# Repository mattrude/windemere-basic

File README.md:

# Windemere Basic 6502 Computer

This is a proof of concept project to build a 65c02 computer from scratch.

This repository is broken up into 2 main sections, [Hardware](Hardware#readme) and [Software](SourceCode#readme).

## About

                 ┌───────────────────────────┐
                 │    WD65C02 Memory Map     │
                 ├───────┬───────────────────┤
                 │ $0000 │                   │
                 │       │   Zero Page RAM   │
                 │ $00ff │                   │
                 ├───────┼───────────────────┤
                 │ $0100 │///////////////////│
                 │       │////// Stack //////│
                 │ $01ff │///////////////////│
                 ├───────┼───────────────────┤
                 │ $0200 │                   │
                 │       │        RAM        │
                 │ $5fff │                   │
                 ├───────┼───────────────────┤
                 │ $6000 │                   │
                 │       │    W65C22S VIA    │
                 │ $600f │                   │
                 ├───────┼───────────────────┤
                 │ $6010 │                   │
                 │       │    (Not Used)     │
                 │ $7fff │                   │
                 ├───────┼───────────────────┤
                 │ $8000 │                   │
                 │       │        ROM        │
                 │ $ffff │                   │
                 └───────┴───────────────────┘

     ┌────────────────────────────────────────────────────────┐
     │                 Zero Page RAM Locations                │
     ├────────────────────────────────────────────────────────┤
     │ 0000: -- -- -- -- -- -- -- --  -- -- -- -- -- -- -- -- │
     │ 0010: -- -- -- -- -- -- -- --  -- -- -- -- -- -- -- -- │
     │ 0020: -- -- -- -- -- -- -- --  -- -- -- -- -- -- -- -- │
     │ 0030: -- -- -- -- -- -- -- --  -- -- -- -- -- -- -- -- │
     │ 0040: -- -- -- -- -- -- -- --  -- -- -- -- -- -- -- -- │
     │ 0050: -- -- -- -- -- -- -- --  -- -- -- -- -- -- -- -- │
     │ 0060: -- -- -- -- -- -- -- --  -- -- -- -- -- -- -- -- │
     │ 0070: -- -- -- -- -- -- -- --  -- -- -- -- -- -- -- -- │
     │ 0080: -- -- -- -- -- -- -- --  -- -- -- -- -- -- -- -- │
     │ 0090: -- -- -- -- -- -- -- --  -- -- -- -- -- -- -- -- │
     │ 00a0: -- -- -- -- -- -- -- --  -- -- -- -- -- -- -- -- │
     │ 00b0: -- -- -- -- -- -- -- --  -- -- -- -- -- -- -- -- │
     │ 00c0: -- -- -- -- -- -- -- --  -- -- -- -- -- -- -- -- │
     │ 00d0: -- -- -- -- -- -- -- --  -- -- -- -- -- -- -- -- │
     │ 00e0: -- -- -- -- -- -- -- --  -- -- -- -- -- -- -- -- │
     │ 00f0: 00 00 00 00 00 00 00 00  -- -- -- -- -- -- -- -- │
     └────────────────────────────────────────────────────────┘

## Required Tools/Software

### Software Used

* [KiCad](https://www.kicad.org/) - To create the Schematic and PCB
* [vasm](http://sun.hasenbraten.de/vasm/) - To compile the Source Code
* [miniPro](https://gitlab.com/DavidGriffith/minipro) - To upload the compiled binary to an eeprom
* [ClickCharts](https://www.nchsoftware.com/chart/index.html) - To create flowchart's for project documentation.

### Compiling from source

This source file expects the use of the vasm compiler found at: [sun.hasenbraten.de/vasm](http://sun.hasenbraten.de/vasm/)

To compile this code, run a command similer to:

    vasm6502_oldstyle -c02 -dotdir -Fbin main.asm -o main.bin

## System Images

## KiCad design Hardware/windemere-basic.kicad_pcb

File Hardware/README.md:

# Hardware

The file describes the layout of the board and how components are used.

## Control Logic

The control logic enables the different components connected to the registry according to the address requested by the 65C02 CPU. We accomplish this primarily by using 3 channels of a 4 channel NAND gate, the [74LS00](https://www.ti.com/lit/gpn/sn74ls00).

1. We start by flipping the bit of `A15` registry line by using two gates of a NAND gate. The inverted output is sent first to the `CS` (chip select) line of the EEPROM. This enables the ROM when the address requested on the registry bus is `$8000` or above and disables the chip when the address is below `$7FFF`.

2. The above inverted `A15` line from the NAND gate continues to one channel of a second NAND gate.  The other channel of this gate is connected to the `PHI2` clock signal, with it's output connected to the `CS` pin of the RAM chip.  The ROM chip also has it's `OE` (output enabled) pin connected to `A14`.  The `OE` pin is active low, so the RAM chip is only active between `$0000` to `$4FFF`.

3. The same inverted `A15` line from the first NAND gate is used a third time, this time in coordination with the `A14` line.  The output from this third gate connects to the `CS` pin of the WD65C22 VIA chip, enabling access in the `$6000`

## W65C22 VIA

The [W65C22](https://www.westerndesigncenter.com/wdc/documentation/w65c22.pdf) Versatile Interface Adapter (VIA) is a flexible I/O device used to connect to the [LCD Screen](#lcd-screen), [20-Button Keypad](#20-button-keypad) and used in software for it's timers.

As described in part 3 of the control logic section above, the VIA chip is accessed within the `$6000` address block.

```armasm
lda #$ff                ; Set all pins on port "B" to output
sta $6002               ; Store to port B on the W65C22
lda #$e1                ; top 3 pins/last, port "A" to output
sta $6003               ; Store to port A on the W65C22
```

## LCD Screen

The liquid crystal display (LCD) screen module is a Hitachi [HD44780](https://www.sparkfun.com/datasheets/LCD/HD44780.pdf) LCD controller is an alphanumeric dot matrix LCD controller developed by Hitachi in the 1980s. The character set of the controller includes ASCII characters, Japanese Kana characters, and some symbols in two 40 character lines.

```armasm
; To initialize the LCD screen via the W65C22

PORTB = $6000               ; W65C22 Register "B"
PORTA = $6001               ; W65C22 Register "A"
DDRB  = $6002               ; W65C22 Data Direction Register "B"
DDRA  = $6003               ; W65C22 Data Direction Register "A"
EN    = $80                 ; HD44780U LCD Starts data read/write
RW    = $40                 ; HD44780U LCD Enables Screen to read data
RS    = $20                 ; HD44780U LCD Registers Select

lcd_init:
    lda #$ff                ; Set all pins on port "B" to output
    sta DDRB
    lda #$e1                ; top 3 pins/last, port "A" to output
    sta DDRA
    lda #$38                ; 8-bit mode; 2-line display; 5x8 font
    jsr lcd_config
    lda #$c                 ; Display on; cursor on; blink off
    jsr lcd_config
    lda #$6                 ; Increment and shift cursor
    jsr lcd_config
    lda #$11                ; Clear the LCD display
    jsr lcd_config
    lda #$2                 ; Send cursor to line 1
    jsr lcd_config
loop:
    jmp loop                ; INIT is now complete

lcd_config:
    jsr lcd_wait             ; Jump to the lcd_wait subroutine
    sta PORTB
    lda #0                  ; Clear LCD RS/RW/EN bits
    sta PORTA
    lda #EN                 ; Set LCD EN (enable) bit
    sta PORTA
    lda #0                  ; Clear LCD RS/RW/EN bits
    sta PORTA
    rts                     ; Return from Subroutine

lcd_wait:
    pha                     ; Push Accumulator to Stack
    lda #%00000000          ; Set Port B as an input
    sta DDRB                ; Load the setting to Port "B"
lcd_busy:
    lda #RW                 ; Set port to Read/Write
    sta PORTA               ; Load the setting to Port "A"
    lda #(RW | EN)          ; Set port to Read/Write & Enable
    sta PORTA               ; Load the setting to Port "A"
    lda PORTB               ; Load Accumulator with Port "B"
    and #%10000000          ; Combine the above with $80
    bne lcd_busy            ; Jump back to the top of lcd_busy
    lda #RW                 ; Set port to Read/Write
    sta PORTA               ; Load the setting to Port "A"
    lda #%11111111          ; Port B is output
    sta DDRB                ; Load the setting to Port "B"
    pla                     ; Pull Accumulator from Stack
    rts                     ; Return from Subroutine
```

## 20-Button Keypad

For the 20-button keypad we use the [MM74C923](https://mm.digikey.com/Volume0/opasdata/d220001/medias/docus/1001/MM74C922,923.pdf) 20-Key Encoder connected to the above W65C22 VIA chip.

When a button is pressed, the chip will set the output as described below and set the `DA` (Data Available) pin, connected to the `CA1` pin on the W65C22, to high.

| W65C22 VIA  | MM74C923   |
| ----------- | ---------- |
| PA0 (pin 2) | A (pin 19) |
| PA1 (pin 3) | B (pin 18) |
| PA2 (pin 4) | C (pin 17) |
| PA3 (pin 5) | D (pin 16) |
| PA4 (pin 6) | E (pin 15) |

Below is a Simple key map with the left hand column showing the pin id as described above and the top row is the button id pressed.

|   | 0 | 1 | 2 | 3 | 4 | 5 | 6 | 7 | 8 | 9 | 10 | 11 | 12 | 13 | 14 | 15 | 16 | 17 | 18 | 19 |
|---|---|---|---|---|---|---|---|---|---|---|----|----|----|----|----|----|----|----|----|----|
| A | - | 1 | - | 1 | - | 1 | - | 1 | - | 1 | -  | 1  | -  | 1  | -  | 1  | -  | 1  | -  | 1  |
| B | - | - | 1 | 1 | - | - | 1 | 1 | - | - | 1  | 1  | -  | -  | 1  | 1  | -  | -  | 1  | 1  |
| C | - | - | - | - | 1 | 1 | 1 | 1 | - | - | -  | -  | 1  | 1  | 1  | 1  | -  | -  | -  | -  |
| D | - | - | - | - | - | - | - | - | 1 | 1 | 1  | 1  | 1  | 1  | 1  | 1  | -  | -  | -  | -  |
| E | - | - | - | - | - | - | - | - | - | - | -  | -  | -  | -  | -  | -  | 1  | 1  | 1  | 1  |

## Reset Circuit

The reset circuit consist of a [MCP102-475](https://www.microchip.com/en-us/product/mcp102) voltage supervisor device designed to keep a processor in reset until the system voltage has reached and stabilized at the proper level 4.75 volts for 120ms.

## References & Notes

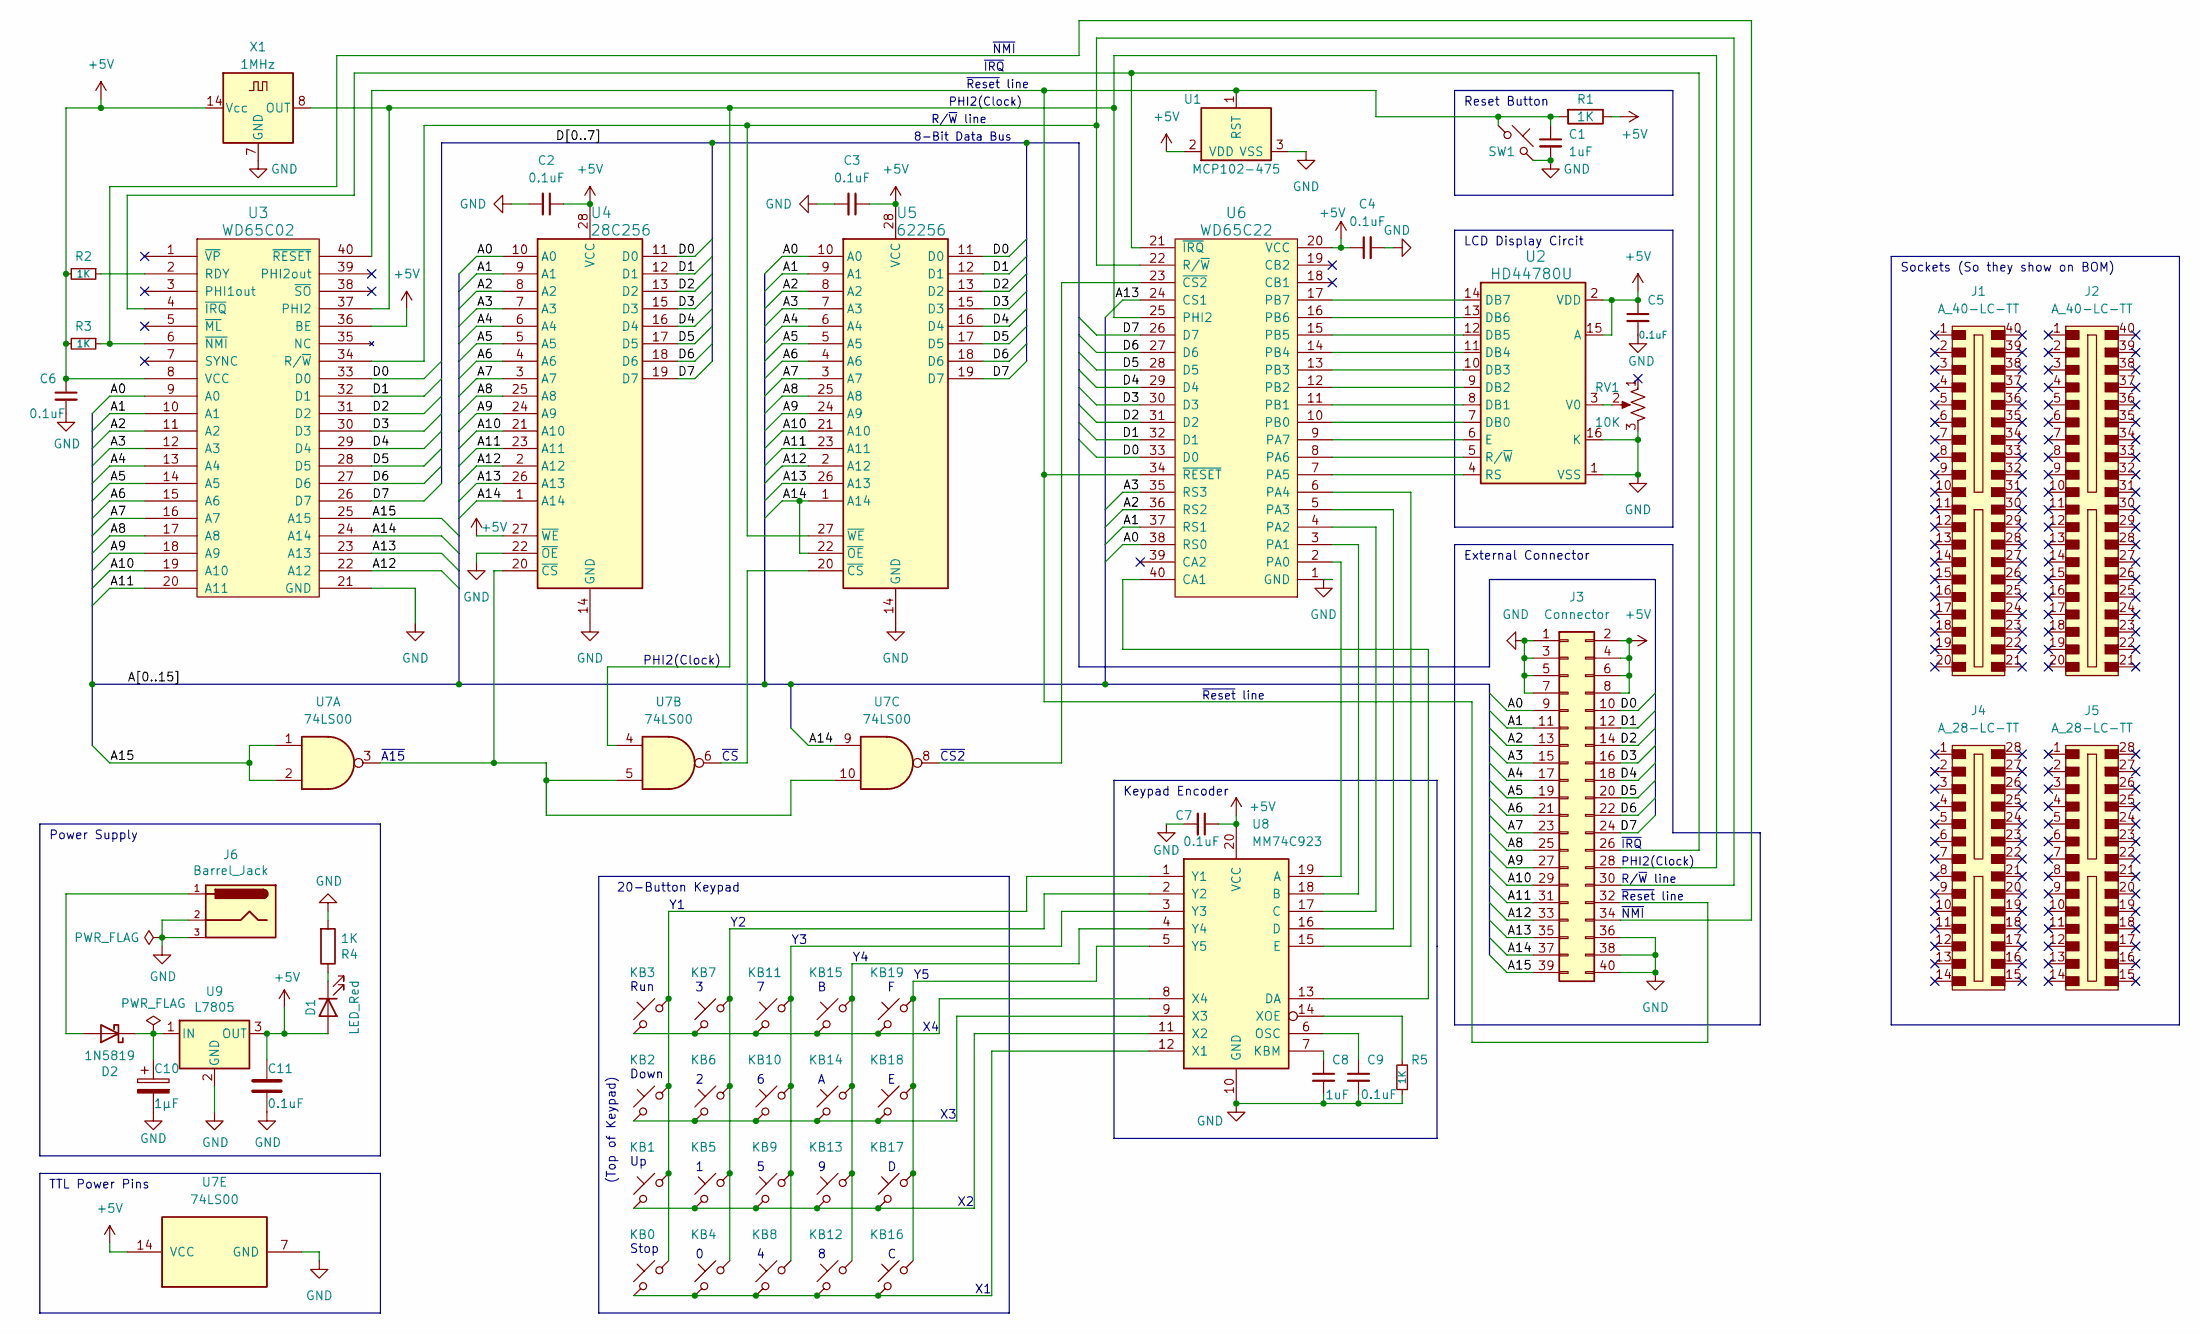
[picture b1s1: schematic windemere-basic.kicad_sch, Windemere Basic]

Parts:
C1, C8: 1uF; C_Disc_D7.0mm_W2.5mm_P5.00mm; Mouser Part 80-C322C105K5R9170-R; Digikey Part 399-13743-1-ND
C2, C3, C4, C5, C6, C7, C9, C11: 0.1uF; C_Disc_D7.0mm_W2.5mm_P5.00mm; Mouser Part 80-C322C104K5R-TR; Digikey Part 399-9877-1-ND
C10: 1µF; C_Radial_D4.0mm_H7.0mm_P1.50mm; Mouser Part 80-ESC105M050AC3AA; Digikey Part 493-11321-3-ND
D1: LED_Red; LED_D5.0mm; Mouser Part 859-LTL-10223W; Digikey Part 160-1087-ND
D2: 1N5819; D_DO-41_SOD81_P10.16mm_Horizontal; Mouser Part 863-1N5819G; Digikey Part 1N5819GOS-ND
J1, J2: A_40-LC-TT; Socket_DIP-40_15.24mm_Conn; Mouser Part 517-4840-6004-CP; Digikey Part ED90059-ND
J3: Connector; PinHeader_2x20_P2.54mm_Vertical; Mouser Part 855-M20-9982045; Digikey Part 732-5310-ND
J4, J5: A_28-LC-TT; Socket_DIP-28_15.24mm_Conn; Mouser Part 517-4828-3004-CP; Digikey Part ED90057-ND
J6: Barrel_Jack; BarrelJack_Horizontal; Mouser Part 490-PJ-018H; Digikey Part CP-018H-ND
KB0, KB1, KB2, KB3, KB4, KB5, KB6, KB7, KB8, KB9, KB10, KB11, KB12, KB13, KB14, KB15, KB16, KB17, KB18, KB19: Push_Button; SW_Cherry_MX_1.00u_PCB; Mouser Part 540-MX1A-11NN; Digikey Part CH162-ND
R1, R2, R3, R4, R5: 1K; R_Axial_DIN0207_L6.3mm_D2.5mm_P10.16mm_Horizontal; Mouser Part 660-CFP1/4CT52R102J; Digikey Part CF14JT1K00CT-ND
RV1: 10K; Potentiometer_Bourns_3296W_Vertical; Mouser Part 81-PV36W103C01B00; Digikey Part 490-2875-ND
SW1: Reset Button; SW_PUSH_6mm; Mouser Part 611-D6R90LFS; Digikey Part 401-1978-ND
U1: MCP102-475; TO-92; Mouser Part 579-MCP102-475E/TO; Digikey Part MCP102-475E/TO-ND
U2: HD44780U; WC1602A; Mouser Part 485-181; Digikey Part 2470-ACM1602KC-NLW-BBW-R-ND
U3: WD65C02; DIP-40_W15.24mm; Mouser Part 955-W65C02S6TPG-14
U4: 28C256; eeprom_socket; Mouser Part 556-AT28C25615PU; Digikey Part AT28C256-15PU-ND
U5: 62256; DIP-28_W15.24mm; Mouser Part 913-AS6C62256-55PCN; Digikey Part 1450-1033-ND
U6: WD65C22; DIP-40_W15.24mm; Mouser Part 955-W65C22S6TPG-14
U7: 74LS00; DIP-14_W7.62mm; Mouser Part 595-CD74HC00E; Digikey Part 2156-CD74HC00E-HC-ND
U8: MM74C923; DIP-20_W7.62mm
U9: L7805; TO-220-3_Horizontal_TabDown; Mouser Part 511-L7805CV; Digikey Part 497-1443-5-ND
X1: 1MHz; Oscillator_DIP-14; Mouser Part 520-TCF100-X; Digikey Part X937-ND

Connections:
+5V: C2.1, C3.1, C4.1, C5.1, C6.1, C7.1, C11.1, D1.2 (A), J3.2, J3.4, J3.6, J3.8, R1.1, R2.2, R3.2, U1.2 (VDD), U2.2 (VDD), U2.15 (A), U3.8 (VCC), U3.36 (BE), U4.27 (~WE), U4.28 (VCC), U5.28 (VCC), U6.20 (VCC), U7.14 (VCC), U8.20 (VCC), U9.3 (OUT), X1.14 (Vcc)
/A0: J3.9, U3.9 (A0), U4.10 (A0), U5.10 (A0), U6.38 (RS0)
/A1: J3.11, U3.10 (A1), U4.9 (A1), U5.9 (A1), U6.37 (RS1)
/A2: J3.13, U3.11 (A2), U4.8 (A2), U5.8 (A2), U6.36 (RS2)
/A3: J3.15, U3.12 (A3), U4.7 (A3), U5.7 (A3), U6.35 (RS3)
/A4: J3.17, U3.13 (A4), U4.6 (A4), U5.6 (A4)
/A5: J3.19, U3.14 (A5), U4.5 (A5), U5.5 (A5)
/A6: J3.21, U3.15 (A6), U4.4 (A6), U5.4 (A6)
/A7: J3.23, U3.16 (A7), U4.3 (A7), U5.3 (A7)
/A8: J3.25, U3.17 (A8), U4.25 (A8), U5.25 (A8)
/A9: J3.27, U3.18 (A9), U4.24 (A9), U5.24 (A9)
/A10: J3.29, U3.19 (A10), U4.21 (A10), U5.21 (A10)
/A11: J3.31, U3.20 (A11), U4.23 (A11), U5.23 (A11)
/A12: J3.33, U3.22 (A12), U4.2 (A12), U5.2 (A12)
/A13: J3.35, U3.23 (A13), U4.26 (A13), U5.26 (A13), U6.24 (CS1)
/A14: J3.37, U3.24 (A14), U4.1 (A14), U5.1 (A14), U5.22 (~OE), U7.9
/A15: J3.39, U3.25 (A15), U7.1, U7.2
/D0: J3.10, U3.33 (D0), U4.11 (D0), U5.11 (D0), U6.33 (D0)
/D1: J3.12, U3.32 (D1), U4.12 (D1), U5.12 (D1), U6.32 (D1)
/D2: J3.14, U3.31 (D2), U4.13 (D2), U5.13 (D2), U6.31 (D2)
/D3: J3.16, U3.30 (D3), U4.15 (D3), U5.15 (D3), U6.30 (D3)
/D4: J3.18, U3.29 (D4), U4.16 (D4), U5.16 (D4), U6.29 (D4)
/D5: J3.20, U3.28 (D5), U4.17 (D5), U5.17 (D5), U6.28 (D5)
/D6: J3.22, U3.27 (D6), U4.18 (D6), U5.18 (D6), U6.27 (D6)
/D7: J3.24, U3.26 (D7), U4.19 (D7), U5.19 (D7), U6.26 (D7)
GND: C1.2, C2.2, C3.2, C4.2, C5.2, C6.2, C7.2, C8.2, C9.2, C10.2, C11.2, J3.1, J3.3, J3.5, J3.7, J3.36, J3.38, J3.40, J6.2, J6.3, R4.2, R5.1, RV1.3, SW1.1, U1.3 (VSS), U2.1 (VSS), U2.16 (K), U3.21 (GND), U4.14 (GND), U4.22 (~OE), U5.14 (GND), U6.1 (GND), U7.7 (GND), U8.10 (GND), U9.2 (GND), X1.7 (GND); also elsewhere on the board
unnamed: D1.1 (K), R4.1
unnamed: D2.2 (A), J6.1
unnamed: C10.1, D2.1 (K), U9.1 (IN)
unnamed: J3.26, U3.4 (~IRQ), U6.21 (~IRQ)
unnamed: J3.28, U3.37 (PHI2), U6.25 (PHI2), U7.4, X1.8 (OUT)
unnamed: J3.30, U3.34 (R/~W), U5.27 (~WE), U6.22 (R/~W)
unnamed: C1.1, J3.32, R1.2, SW1.2, U1.1 (RST), U3.40 (~RESET), U6.34 (~RESET)
unnamed: J3.34, R3.1, U3.6 (~NMI)
unnamed: U2.7 (DB0), U6.10 (PB0)
unnamed: U2.8 (DB1), U6.11 (PB1)
unnamed: U2.9 (DB2), U6.12 (PB2)
unnamed: U2.10 (DB3), U6.13 (PB3)
unnamed: U2.11 (DB4), U6.14 (PB4)
unnamed: U2.12 (DB5), U6.15 (PB5)
unnamed: U2.13 (DB6), U6.16 (PB6)
unnamed: U2.14 (DB7), U6.17 (PB7)
unnamed: U2.6 (E), U6.9 (PA7)
unnamed: U2.4 (RS), U6.7 (PA5)
unnamed: U2.5 (R/~W), U6.8 (PA6)
unnamed: RV1.2, U2.3 (V0)
unnamed: R2.1, U3.2 (RDY)
unnamed: U4.20 (~CS), U7.3, U7.5, U7.10
unnamed: U5.20 (~CS), U7.6
unnamed: U6.40 (CA1), U8.13 (DA)
unnamed: U6.2 (PA0), U8.19 (A)
unnamed: U6.3 (PA1), U8.18 (B)
unnamed: U6.4 (PA2), U8.17 (C)
unnamed: U6.5 (PA3), U8.16 (D)
unnamed: U6.6 (PA4), U8.15 (E)
unnamed: U6.23 (~CS2), U7.8
unnamed: C8.1, U8.7 (KBM)
unnamed: C9.1, U8.6 (OSC)
unnamed: KB0.1, KB4.1, KB8.1, KB12.1, KB16.1, U8.12 (X1)
unnamed: KB1.1, KB5.1, KB9.1, KB13.1, KB17.1, U8.11 (X2)
unnamed: KB2.1, KB6.1, KB10.1, KB14.1, KB18.1, U8.9 (X3)
unnamed: KB3.1, KB7.1, KB11.1, KB15.1, KB19.1, U8.8 (X4)
unnamed: R5.2, U8.14 (XOE)
unnamed: KB0.2, KB1.2, KB2.2, KB3.2, U8.1 (Y1)
unnamed: KB4.2, KB5.2, KB6.2, KB7.2, U8.2 (Y2)
unnamed: KB8.2, KB9.2, KB10.2, KB11.2, U8.3 (Y3)
unnamed: KB12.2, KB13.2, KB14.2, KB15.2, U8.4 (Y4)
unnamed: KB16.2, KB17.2, KB18.2, KB19.2, U8.5 (Y5)

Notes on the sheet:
Sockets (So they show on BOM)
PHI2(Clock)
20-Button Keypad
(Top of Keypad)
LCD Display Circit
Keypad Encoder
~{Reset} line
Stop
8-Bit Data Bus
Run
~{CS2}
Power Supply
~{IRQ}
~{A15}
Down
Reset Button
R/~{W} line
External Connector
~{NMI}
TTL Power Pins
~{CS}

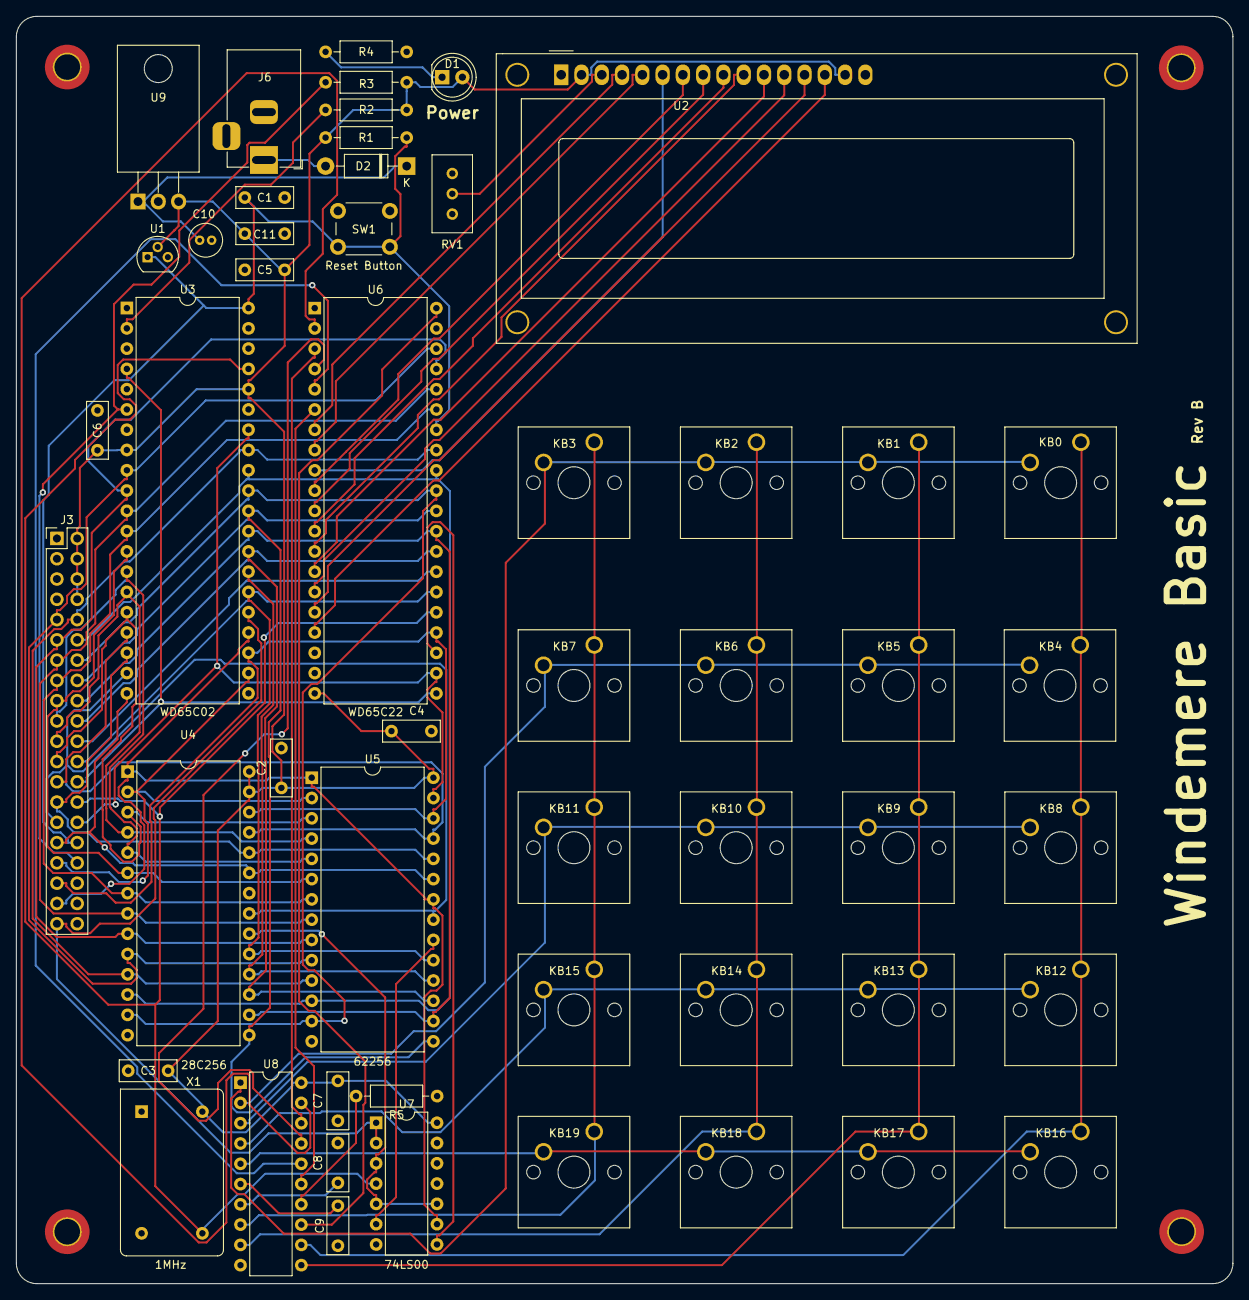
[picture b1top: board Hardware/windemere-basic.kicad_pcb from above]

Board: 2 copper layers, 152.4 x 158.8 mm, 57 parts (0 on the bottom side), 68 nets.

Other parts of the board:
REF1, REF2, REF3, REF4: MountingHole_3.2mm_M3_DIN965_Pad_TopBottom
memory_map: 6502-Memory_Map

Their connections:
GND: REF1.1, REF2.1, REF3.1, REF4.1; also elsewhere on the board

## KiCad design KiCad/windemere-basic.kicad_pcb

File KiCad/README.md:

# Hardware

The file describes the layout of the board and how components are used.

## Control Logic

4 channel NAND gate the [SN74LS00](https://www.ti.com/lit/gpn/sn74ls00)

## Buzzer

The buzzer uses the 6522's PB7 and free-running T1 to output a modulation needed to create sound.[^1][^2]

```text
You can use the 6522's PB7 and free-running T1 to output a beep signal,
or clock out an exact number of cycles from an arbitrary waveform generator,
while leaving the µP free to do other things at the same time.

You'll need the 2 msb's of the 6522's ACR to be 11. You might use a timer
interrupt to turn off the beep, or a cycle-counting interrupt to stop
the arb at the right time.
```

A code example from Jeff Tranter:[^1]

```asm
  COUNT = $4119
      
  LDA #$00
  STA IER             ; disable all interrupts
  LDA #%11000000
  STA ACR             ; Set to T1 free running PB7 enabled
  LDA #<COUNT
  STA T1CL            ; Low byte of count
  LDA #>COUNT
  STA T1CH            ; High byte of count
  RTS
```

## LCD Screen

## LED Lights

## 20-Button Keypad

## Reset Circit

**References & Notes**
[^1]: [6522 VIA Experiment #2](http://jefftranter.blogspot.com/2012/03/6522-via-experiment-2.html)
[^2]: [Tip of the day #17](http://forum.6502.org/viewtopic.php?f=7&t=342&start=17)

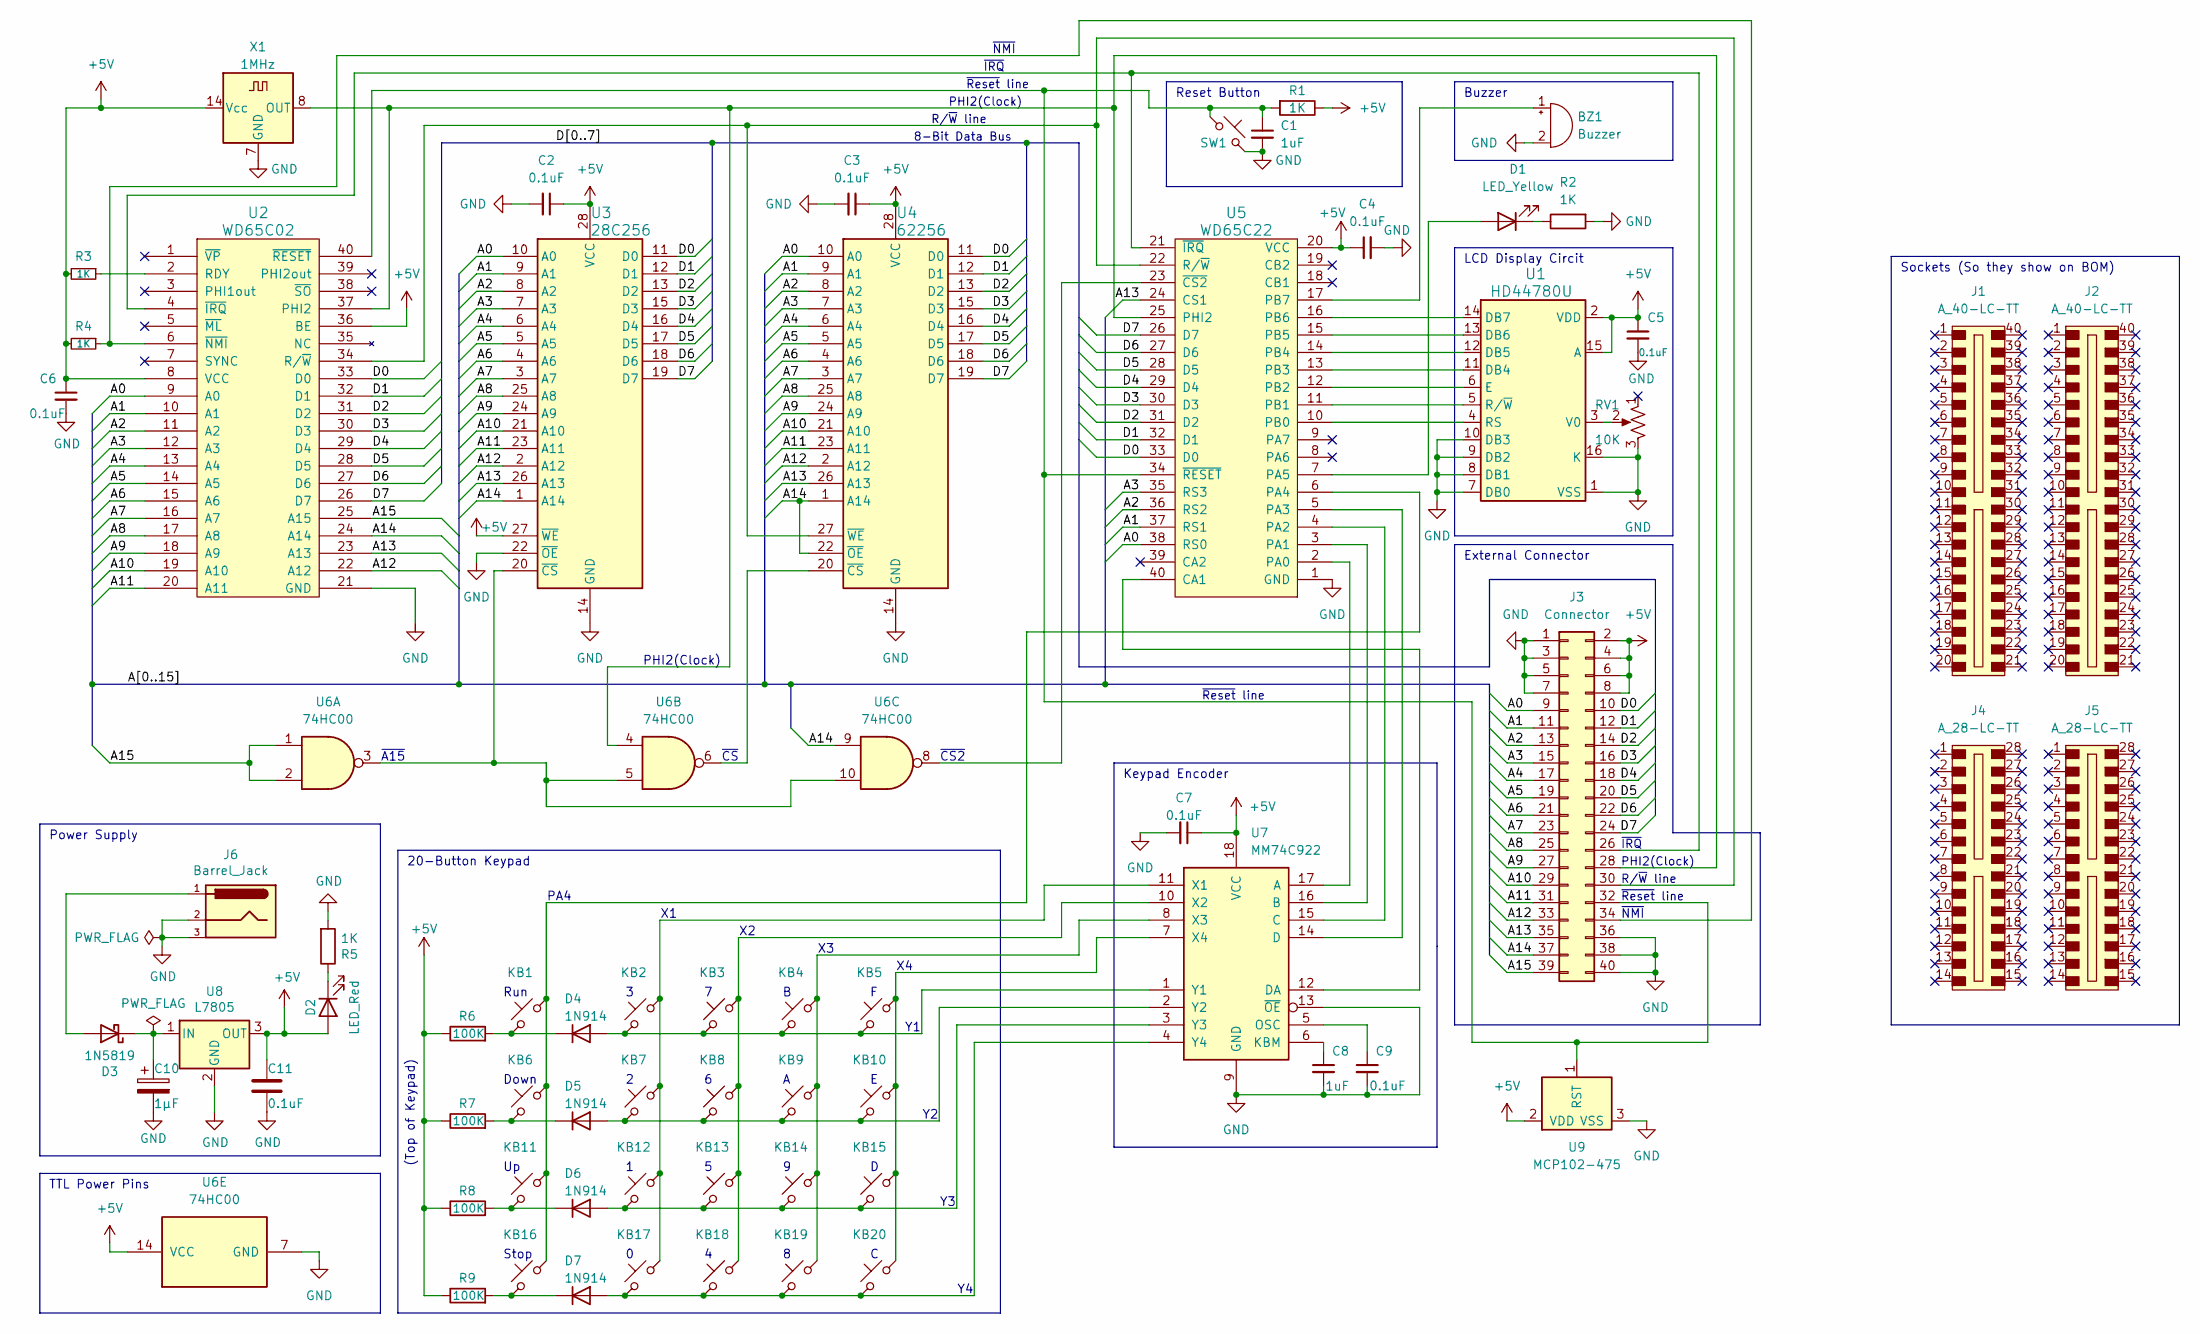
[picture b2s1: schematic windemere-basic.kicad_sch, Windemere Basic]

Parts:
BZ1: Buzzer; Buzzer_12x9.5RM7.6; Mouser Part 490-CEM-1212S; Digikey Part 102-1156-ND
C1, C8: 1uF; C_Disc_D7.0mm_W2.5mm_P5.00mm; Mouser Part 80-C322C105K5R9170-R; Digikey Part 399-13743-1-ND
C2, C3, C4, C5, C6, C7, C9, C11: 0.1uF; C_Disc_D7.0mm_W2.5mm_P5.00mm; Mouser Part 80-C322C104K5R-TR; Digikey Part 399-9877-1-ND
C10: 1µF; C_Radial_D4.0mm_H7.0mm_P1.50mm; Mouser Part 80-ESC105M050AC3AA; Digikey Part 493-11321-3-ND
D1: LED_Yellow; LED_D5.0mm; Mouser Part 859-LTL-10223W; Digikey Part 160-1087-ND
D2: LED_Red; LED_D5.0mm; Mouser Part 859-LTL-10223W; Digikey Part 160-1087-ND
D3: 1N5819; D_DO-41_SOD81_P10.16mm_Horizontal; Mouser Part 863-1N5819G; Digikey Part 1N5819GOS-ND
D4, D5, D6, D7: 1N914; D_DO-35_SOD27_P7.62mm_Horizontal; Mouser Part 512-1N914; Digikey Part 1N914FS-ND
J1, J2: A_40-LC-TT; Socket_DIP-40_15.24mm_Conn; Mouser Part 517-4840-6004-CP; Digikey Part ED90059-ND
J3: Connector; PinHeader_2x20_P2.54mm_Vertical; Mouser Part 855-M20-9982045; Digikey Part 732-5310-ND
J4, J5: A_28-LC-TT; Socket_DIP-28_15.24mm_Conn; Mouser Part 517-4828-3004-CP; Digikey Part ED90057-ND
J6: Barrel_Jack; BarrelJack_Horizontal; Mouser Part 490-PJ-018H; Digikey Part CP-018H-ND
KB1, KB2, KB3, KB4, KB5, KB6, KB7, KB8, KB9, KB10, KB11, KB12, KB13, KB14, KB15, KB16, KB17, KB18, KB19, KB20: Push_Button; SW_Cherry_MX_1.00u_PCB; Mouser Part 540-MX1A-11NN; Digikey Part CH162-ND
R1, R2, R3, R4, R5: 1K; R_Axial_DIN0207_L6.3mm_D2.5mm_P10.16mm_Horizontal; Mouser Part 660-CFP1/4CT52R102J; Digikey Part CF14JT1K00CT-ND
R6, R7, R8, R9: 100K; R_Axial_DIN0207_L6.3mm_D2.5mm_P10.16mm_Horizontal; Mouser Part 660-CF1/2CT52R104J; Digikey Part CF14JT100KCT-ND
RV1: 10K; Potentiometer_Bourns_3296W_Vertical; Mouser Part 81-PV36W103C01B00; Digikey Part 490-2875-ND
SW1: Reset Button; SW_PUSH_6mm; Mouser Part 611-D6R90LFS; Digikey Part 401-1978-ND
U1: HD44780U; WC1602A; Mouser Part 485-181; Digikey Part 2470-ACM1602KC-NLW-BBW-R-ND
U2: WD65C02; DIP-40_W15.24mm; Mouser Part 955-W65C02S6TPG-14
U3: 28C256; eeprom_socket; Mouser Part 556-AT28C25615PU; Digikey Part AT28C256-15PU-ND
U4: 62256; DIP-28_W15.24mm; Mouser Part 913-AS6C62256-55PCN; Digikey Part 1450-1033-ND
U5: WD65C22; DIP-40_W15.24mm; Mouser Part 955-W65C22S6TPG-14
U6: 74HC00; DIP-14_W7.62mm; Mouser Part 595-CD74HC00E; Digikey Part 2156-CD74HC00E-HC-ND
U7: MM74C922; DIP-18_W7.62mm
U8: L7805; TO-220-3_Horizontal_TabDown; Mouser Part 511-L7805CV; Digikey Part 497-1443-5-ND
U9: MCP102-475; TO-92; Mouser Part 579-MCP102-475E/TO; Digikey Part MCP102-475E/TO-ND
X1: 1MHz; Oscillator_DIP-14; Mouser Part 520-TCF100-X; Digikey Part X937-ND

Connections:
+5V: C2.1, C3.1, C4.1, C5.1, C6.1, C7.1, C11.1, D2.2 (A), J3.2, J3.4, J3.6, J3.8, R1.1, R3.2, R4.2, R6.1, R7.1, R8.1, R9.1, U1.2 (VDD), U1.15 (A), U2.8 (VCC), U2.36 (BE), U3.27 (~WE), U3.28 (VCC), U4.28 (VCC), U5.20 (VCC), U6.14 (VCC), U7.18 (VCC), U8.3 (OUT), U9.2 (VDD), X1.14 (Vcc)
/A0: J3.9, U2.9 (A0), U3.10 (A0), U4.10 (A0), U5.38 (RS0)
/A1: J3.11, U2.10 (A1), U3.9 (A1), U4.9 (A1), U5.37 (RS1)
/A2: J3.13, U2.11 (A2), U3.8 (A2), U4.8 (A2), U5.36 (RS2)
/A3: J3.15, U2.12 (A3), U3.7 (A3), U4.7 (A3), U5.35 (RS3)
/A4: J3.17, U2.13 (A4), U3.6 (A4), U4.6 (A4)
/A5: J3.19, U2.14 (A5), U3.5 (A5), U4.5 (A5)
/A6: J3.21, U2.15 (A6), U3.4 (A6), U4.4 (A6)
/A7: J3.23, U2.16 (A7), U3.3 (A7), U4.3 (A7)
/A8: J3.25, U2.17 (A8), U3.25 (A8), U4.25 (A8)
/A9: J3.27, U2.18 (A9), U3.24 (A9), U4.24 (A9)
/A10: J3.29, U2.19 (A10), U3.21 (A10), U4.21 (A10)
/A11: J3.31, U2.20 (A11), U3.23 (A11), U4.23 (A11)
/A12: J3.33, U2.22 (A12), U3.2 (A12), U4.2 (A12)
/A13: J3.35, U2.23 (A13), U3.26 (A13), U4.26 (A13), U5.24 (CS1)
/A14: J3.37, U2.24 (A14), U3.1 (A14), U4.1 (A14), U4.22 (~OE), U6.9
/A15: J3.39, U2.25 (A15), U6.1, U6.2
/D0: J3.10, U2.33 (D0), U3.11 (D0), U4.11 (D0), U5.33 (D0)
/D1: J3.12, U2.32 (D1), U3.12 (D1), U4.12 (D1), U5.32 (D1)
/D2: J3.14, U2.31 (D2), U3.13 (D2), U4.13 (D2), U5.31 (D2)
/D3: J3.16, U2.30 (D3), U3.15 (D3), U4.15 (D3), U5.30 (D3)
/D4: J3.18, U2.29 (D4), U3.16 (D4), U4.16 (D4), U5.29 (D4)
/D5: J3.20, U2.28 (D5), U3.17 (D5), U4.17 (D5), U5.28 (D5)
/D6: J3.22, U2.27 (D6), U3.18 (D6), U4.18 (D6), U5.27 (D6)
/D7: J3.24, U2.26 (D7), U3.19 (D7), U4.19 (D7), U5.26 (D7)
GND: BZ1.2 (+), C1.2, C2.2, C3.2, C4.2, C5.2, C6.2, C7.2, C8.2, C9.2, C10.2, C11.2, J3.1, J3.3, J3.5, J3.7, J3.36, J3.38, J3.40, J6.2, J6.3, R2.2, R5.2, RV1.3, SW1.1, U1.1 (VSS), U1.7 (DB0), U1.8 (DB1), U1.9 (DB2), U1.10 (DB3), U1.16 (K), U2.21 (GND), U3.14 (GND), U3.22 (~OE), U4.14 (GND), U5.1 (GND), U6.7 (GND), U7.9 (GND), U7.13 (~OE), U8.2 (GND), U9.3 (VSS), X1.7 (GND); also elsewhere on the board
unnamed: BZ1.1 (-), U5.17 (PB7)
unnamed: D1.2 (A), U5.7 (PA5)
unnamed: D1.1 (K), R2.1
unnamed: D2.1 (K), R5.1
unnamed: D3.2 (A), J6.1
unnamed: C10.1, D3.1 (K), U8.1 (IN)
unnamed: D4.2 (A), KB2.1, KB3.1, KB4.1, KB5.1, U7.1 (Y1)
unnamed: D4.1 (K), KB1.1, R6.2
unnamed: D5.2 (A), KB7.1, KB8.1, KB9.1, KB10.1, U7.2 (Y2)
unnamed: D5.1 (K), KB6.1, R7.2
unnamed: D6.2 (A), KB12.1, KB13.1, KB14.1, KB15.1, U7.3 (Y3)
unnamed: D6.1 (K), KB11.1, R8.2
unnamed: D7.2 (A), KB17.1, KB18.1, KB19.1, KB20.1, U7.4 (Y4)
unnamed: D7.1 (K), KB16.1, R9.2
unnamed: J3.26, U2.4 (~IRQ), U5.21 (~IRQ)
unnamed: J3.28, U2.37 (PHI2), U5.25 (PHI2), U6.4, X1.8 (OUT)
unnamed: J3.30, U2.34 (R/~W), U4.27 (~WE), U5.22 (R/~W)
unnamed: C1.1, J3.32, R1.2, SW1.2, U2.40 (~RESET), U5.34 (~RESET), U9.1 (RST)
unnamed: J3.34, R4.1, U2.6 (~NMI)
unnamed: U1.11 (DB4), U5.13 (PB3)
unnamed: U1.12 (DB5), U5.14 (PB4)
unnamed: U1.13 (DB6), U5.15 (PB5)
unnamed: U1.14 (DB7), U5.16 (PB6)
unnamed: U1.6 (E), U5.12 (PB2)
unnamed: U1.4 (RS), U5.10 (PB0)
unnamed: U1.5 (R/~W), U5.11 (PB1)
unnamed: RV1.2, U1.3 (V0)
unnamed: R3.1, U2.2 (RDY)
unnamed: U3.20 (~CS), U6.3, U6.5, U6.10
unnamed: U4.20 (~CS), U6.6
unnamed: U5.40 (CA1), U7.12 (DA)
unnamed: U5.2 (PA0), U7.17 (A)
unnamed: U5.3 (PA1), U7.16 (B)
unnamed: U5.4 (PA2), U7.15 (C)
unnamed: U5.5 (PA3), U7.14 (D)
unnamed: KB1.2, KB6.2, KB11.2, KB16.2, U5.6 (PA4)
unnamed: U5.23 (~CS2), U6.8
unnamed: C8.1, U7.6 (KBM)
unnamed: C9.1, U7.5 (OSC)
unnamed: KB2.2, KB7.2, KB12.2, KB17.2, U7.11 (X1)
unnamed: KB3.2, KB8.2, KB13.2, KB18.2, U7.10 (X2)
unnamed: KB4.2, KB9.2, KB14.2, KB19.2, U7.8 (X3)
unnamed: KB5.2, KB10.2, KB15.2, KB20.2, U7.7 (X4)

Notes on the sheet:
Sockets (So they show on BOM)
PHI2(Clock)
20-Button Keypad
Buzzer
(Top of Keypad)
LCD Display Circit
Keypad Encoder
~{Reset} line
Stop
8-Bit Data Bus
Run
~{CS2}
Power Supply
~{IRQ}
~{A15}
Down
Reset Button
PA4
R/~{W} line
External Connector
~{NMI}
TTL Power Pins
~{CS}

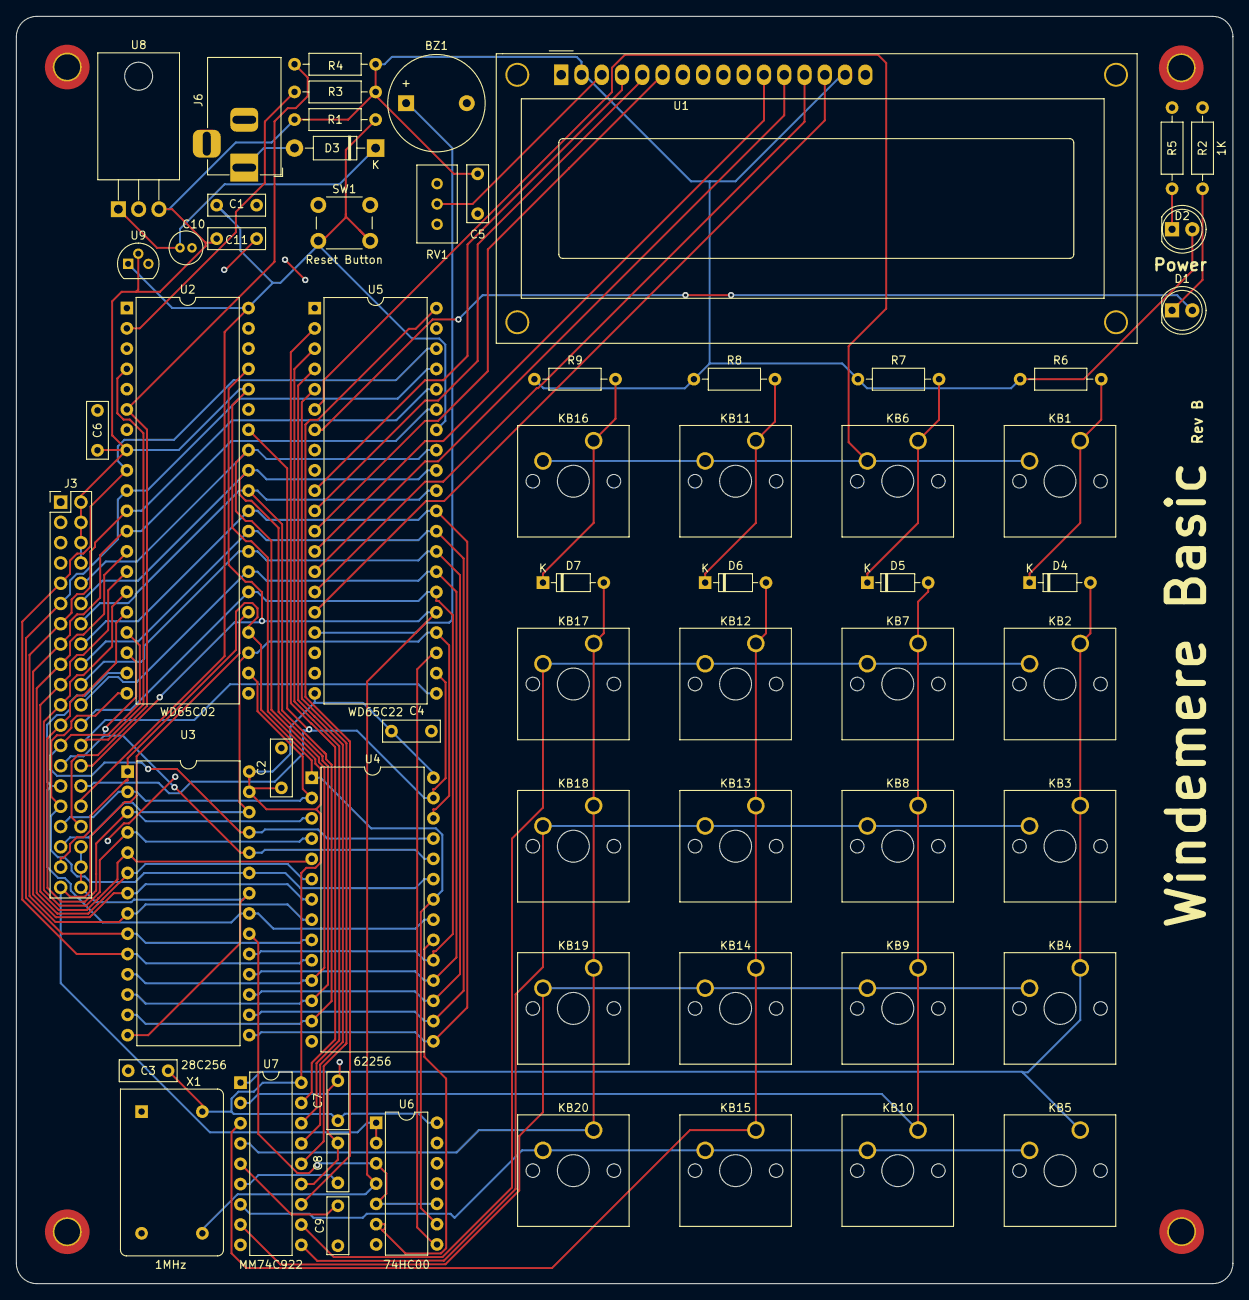
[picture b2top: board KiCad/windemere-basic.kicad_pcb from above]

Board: 2 copper layers, 152.4 x 158.8 mm, 67 parts (0 on the bottom side), 69 nets.

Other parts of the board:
REF1, REF2, REF3, REF4: MountingHole_3.2mm_M3_DIN965_Pad_TopBottom
memory_map: 6502-Memory_Map

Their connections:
GND: REF1.1, REF2.1, REF3.1, REF4.1; also elsewhere on the board

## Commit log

2022-02-08 Starting Out
2022-02-08 Correct Site URL
2022-02-08 Correct drawing sheet name
2022-02-16 footprint updates
2022-03-13 correct issues
2022-03-13 Delete 65xx-mdr2.kicad_sym
    Duplicate
2022-03-15 Add J1
2022-03-15 Added MCP102-475 to reset line
2022-03-15 added pcb image
2022-03-15 Add Datasheets
2022-03-16 Add Digikey Part Numbers
2022-03-16 Create LICENSE
2022-03-16 Update LICENSE
2022-03-16 Add Zif socket to eprom
2022-03-16 update socket
2022-03-16 Create fp-lib-table
2022-03-16 more socket updates
2022-03-16 added tools
2022-03-18 Set Grid origin in KiCad
2022-03-20 update to current
2022-03-20 remove unused
2022-03-20 remove fp-lib-table
2022-03-20 update docs
2022-03-20 Update ID's
2022-03-24 Add Bypass caps
2022-03-24 remove unused files
2022-04-07 set to 80 col
2022-04-07 comment updates
2022-04-07 correct license in readme
2022-07-25 minor footprint changes.
2022-07-26 update symbols
2022-07-28 Cleanup the Schematic
2022-07-29 Added user-interface.asm & user-interface.bin
2022-07-29 create list file
2022-07-29 minor list updates
2022-07-30 Move to Rev B
2022-07-30 Correct buzzer
2022-07-31 correct traces
2022-07-31 update bom & gerber files
2022-08-03 Update comments
2022-08-24 Add Description
2022-09-01 Correct side of keyboard connector
2022-09-06 Add indrect jump example
2022-09-06 Create windemere-basic.code-workspace
2022-09-06 remove unused statements
2022-09-21 Getting ready for release
2022-09-28 Change 28C256 label from fab to silk
2022-09-28 Correct minor spacing
2022-09-28 Minor part number updates
2022-09-29 Update windemere-basic.kicad_pcb
    Minor track updates
2022-09-29 Remove unused text from front
2022-10-03 correct bin & lst files
2022-11-08 Move footprint files
    Move footprint files to their own folder for easier monitoring.
2022-11-08 Update user-interface.asm
    Reword the build script
2022-11-08 Add a small demo LCD program
2022-12-25 white space updates
2022-12-25 4-bit LCD mode
2022-12-25 File name update
2023-06-01 Moving to KiCad 7.0.5
2023-06-07 Minor changes to SourceCode README.md file
2023-06-07 Adding WOZMON
2023-10-22 Migrate to KiCad 7.0.8
2023-10-25 Correct verbiage in comment of sheet
2023-10-31 add output file to gitignore
2023-11-07 Minor cleanup for wozmon.asm
2023-11-08 Move KiCad to Hardware
2023-11-08 Hardware: Change from 74HC00 to 74LS00
2023-11-20 Change to MM74LS923
2023-11-21 Correct MCP102-475 Datasheet
2023-11-23 Hardware Readme Update
2023-11-24 Correct MM74C923
2023-11-24 correct direction of mm74c923
2023-12-13 Add Bypass to 74LS923
2023-12-13 Minor README Updates
2023-12-14 correct table
2023-12-14 set table to a sigle line
2023-12-14 try 2
2023-12-14 try 3
2023-12-14 and I give up
2023-12-14 try somethin new
2023-12-14 now we got something
2023-12-14 LCD Addions
2023-12-14 add note
2023-12-14 correct highlight.js
2024-01-22 Move to KiCad 8.0
2024-01-27 Update windemere-basic.kicad_sch
    correct voltage regulator
2024-02-01 Correct top header spacing
2024-04-11 Spell Checking
2024-04-11 Spell Check - Added Words

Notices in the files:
Hardware/windemere-basic.kicad_pcb:
©2021 by Matt Rude
KiCad/windemere-basic.kicad_pcb:
©2022 by Matt Rude
